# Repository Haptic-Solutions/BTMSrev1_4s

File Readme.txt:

Open Source Universal Battery Controller
Test battery is 4S Lithium Ion Pack
16.8V 2.6Ah rated. 38.48Wh Nominal
Please note that this device is a prototype and all features are still being extensively tested, some features aren't fully implement, and others are awaiting further polishing. Please excuse our mess as we continue to develop this system, it's documentation, and source/design repository.
Watch your step! The workshop is messy. ;)

	Though, this pack is worn out a bit as these are recycled cells. No worries though, as this BMS, Charger, and Power Management System will measure, and account for performance variations between batteries and chemistry types. Features include, but are not limited to:

    • BUCK-BOOST charge input to accommodate a wide range of battery configurations and supports charge voltage inputs from 5v-25v
    • USB-PD and USB2.0 charge to support a wide range of USB chargers up to 100watt.
    • AUX CHARGE PORT for solar applications
    • 2S, 3S, OR 4S support via jumper on the cell inputs
    • POWER SWITCH MODES ranging from push-and-hold, to automatic power on when charger power disconnected
    • FULL ACCESS to a wide range of settings such as cell max voltage and current
    • REDUNDANT SAFETY SYSTEMS not just in firmware but in hardware via over-voltage detection, shutdown, and disabling once any cell reaches 4.3v
    • ERROR REPORTING and TELEMETRY in a simple to access single letter command set via built-in USB serial or AUX UART header accessed by a terminal emulator
    • LCD SUPPORT via UART output that is configurable
    • HEATER CONTROL for cold environments with board and battery temperature sensors

Specs:
    • 25V 5A max charge input
    • 18V 10A max battery output, 2s-4s configurations, max 4.3v/cell
    • Dual UART with one dedicated to USB FTDI
    • dsPIC30F4011 micro-controller ~14mips
    • C codebase
    • 0.015mA deep-sleep (diode leakage, we aim to improve this)

Stay tuned for developments. We've got a lot of ground to cover before we release this into the wild! Our goal is to help other hobbyists be safer with batteries while getting their max performance in a very wide range of supported applications and cell chemistry types!
Copyright (2024) Haptic Solutions Inc.

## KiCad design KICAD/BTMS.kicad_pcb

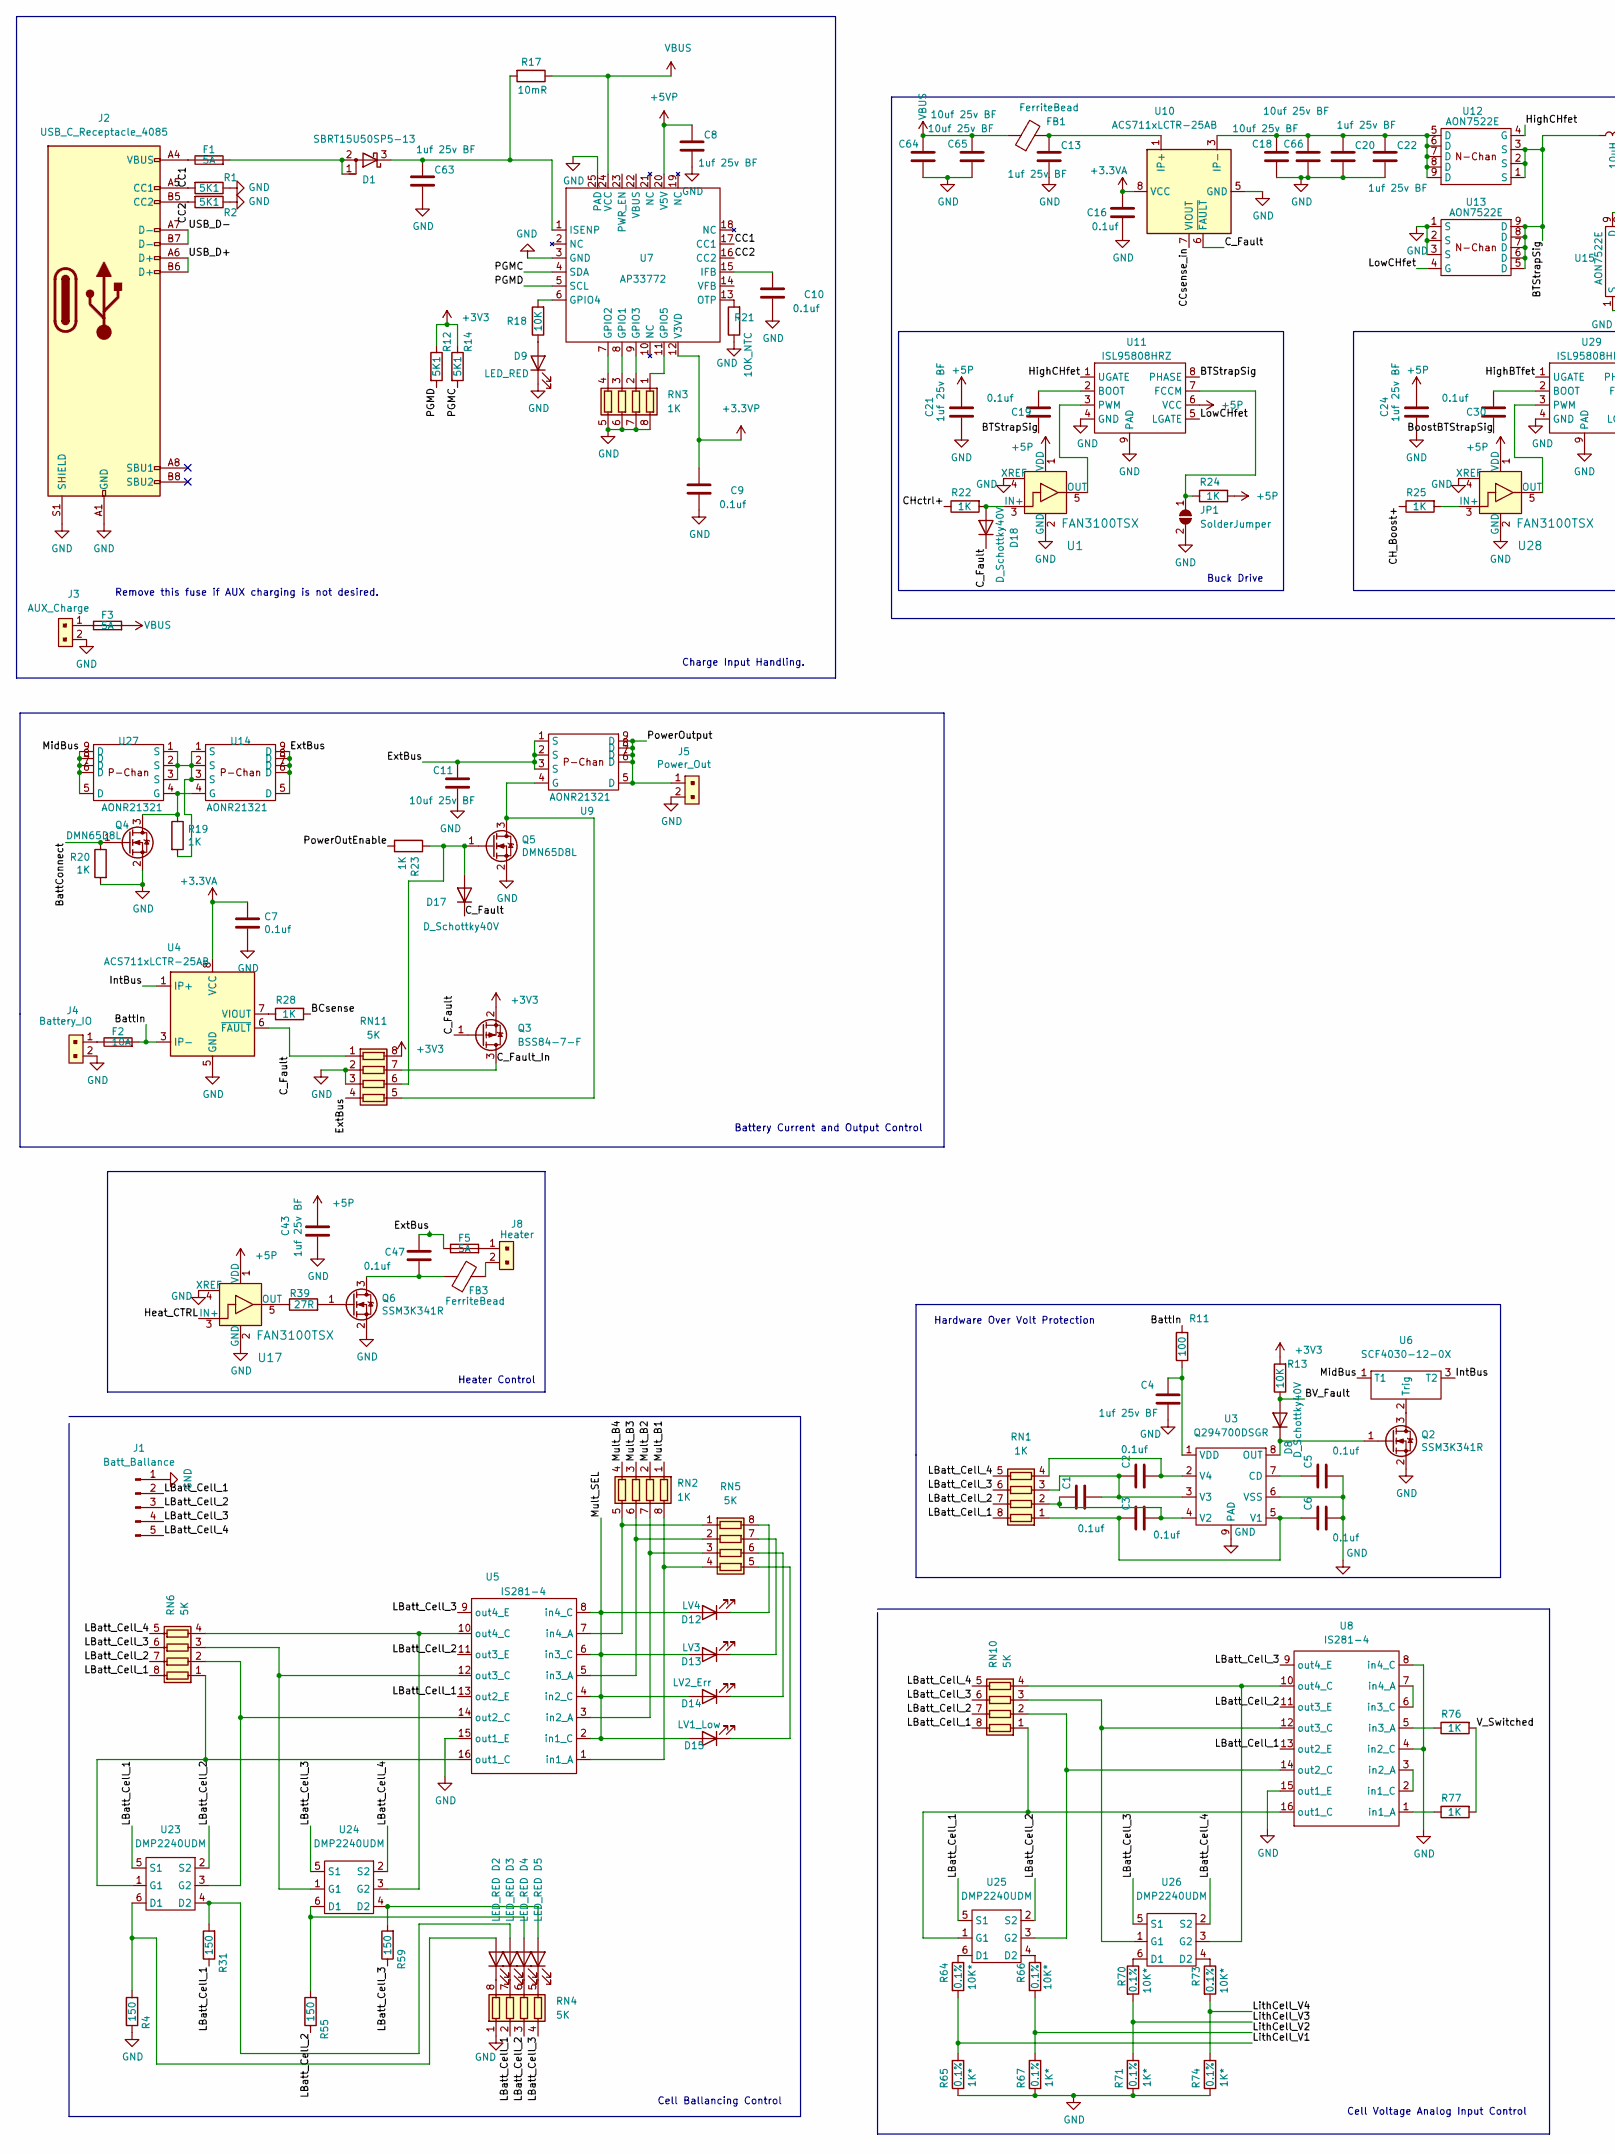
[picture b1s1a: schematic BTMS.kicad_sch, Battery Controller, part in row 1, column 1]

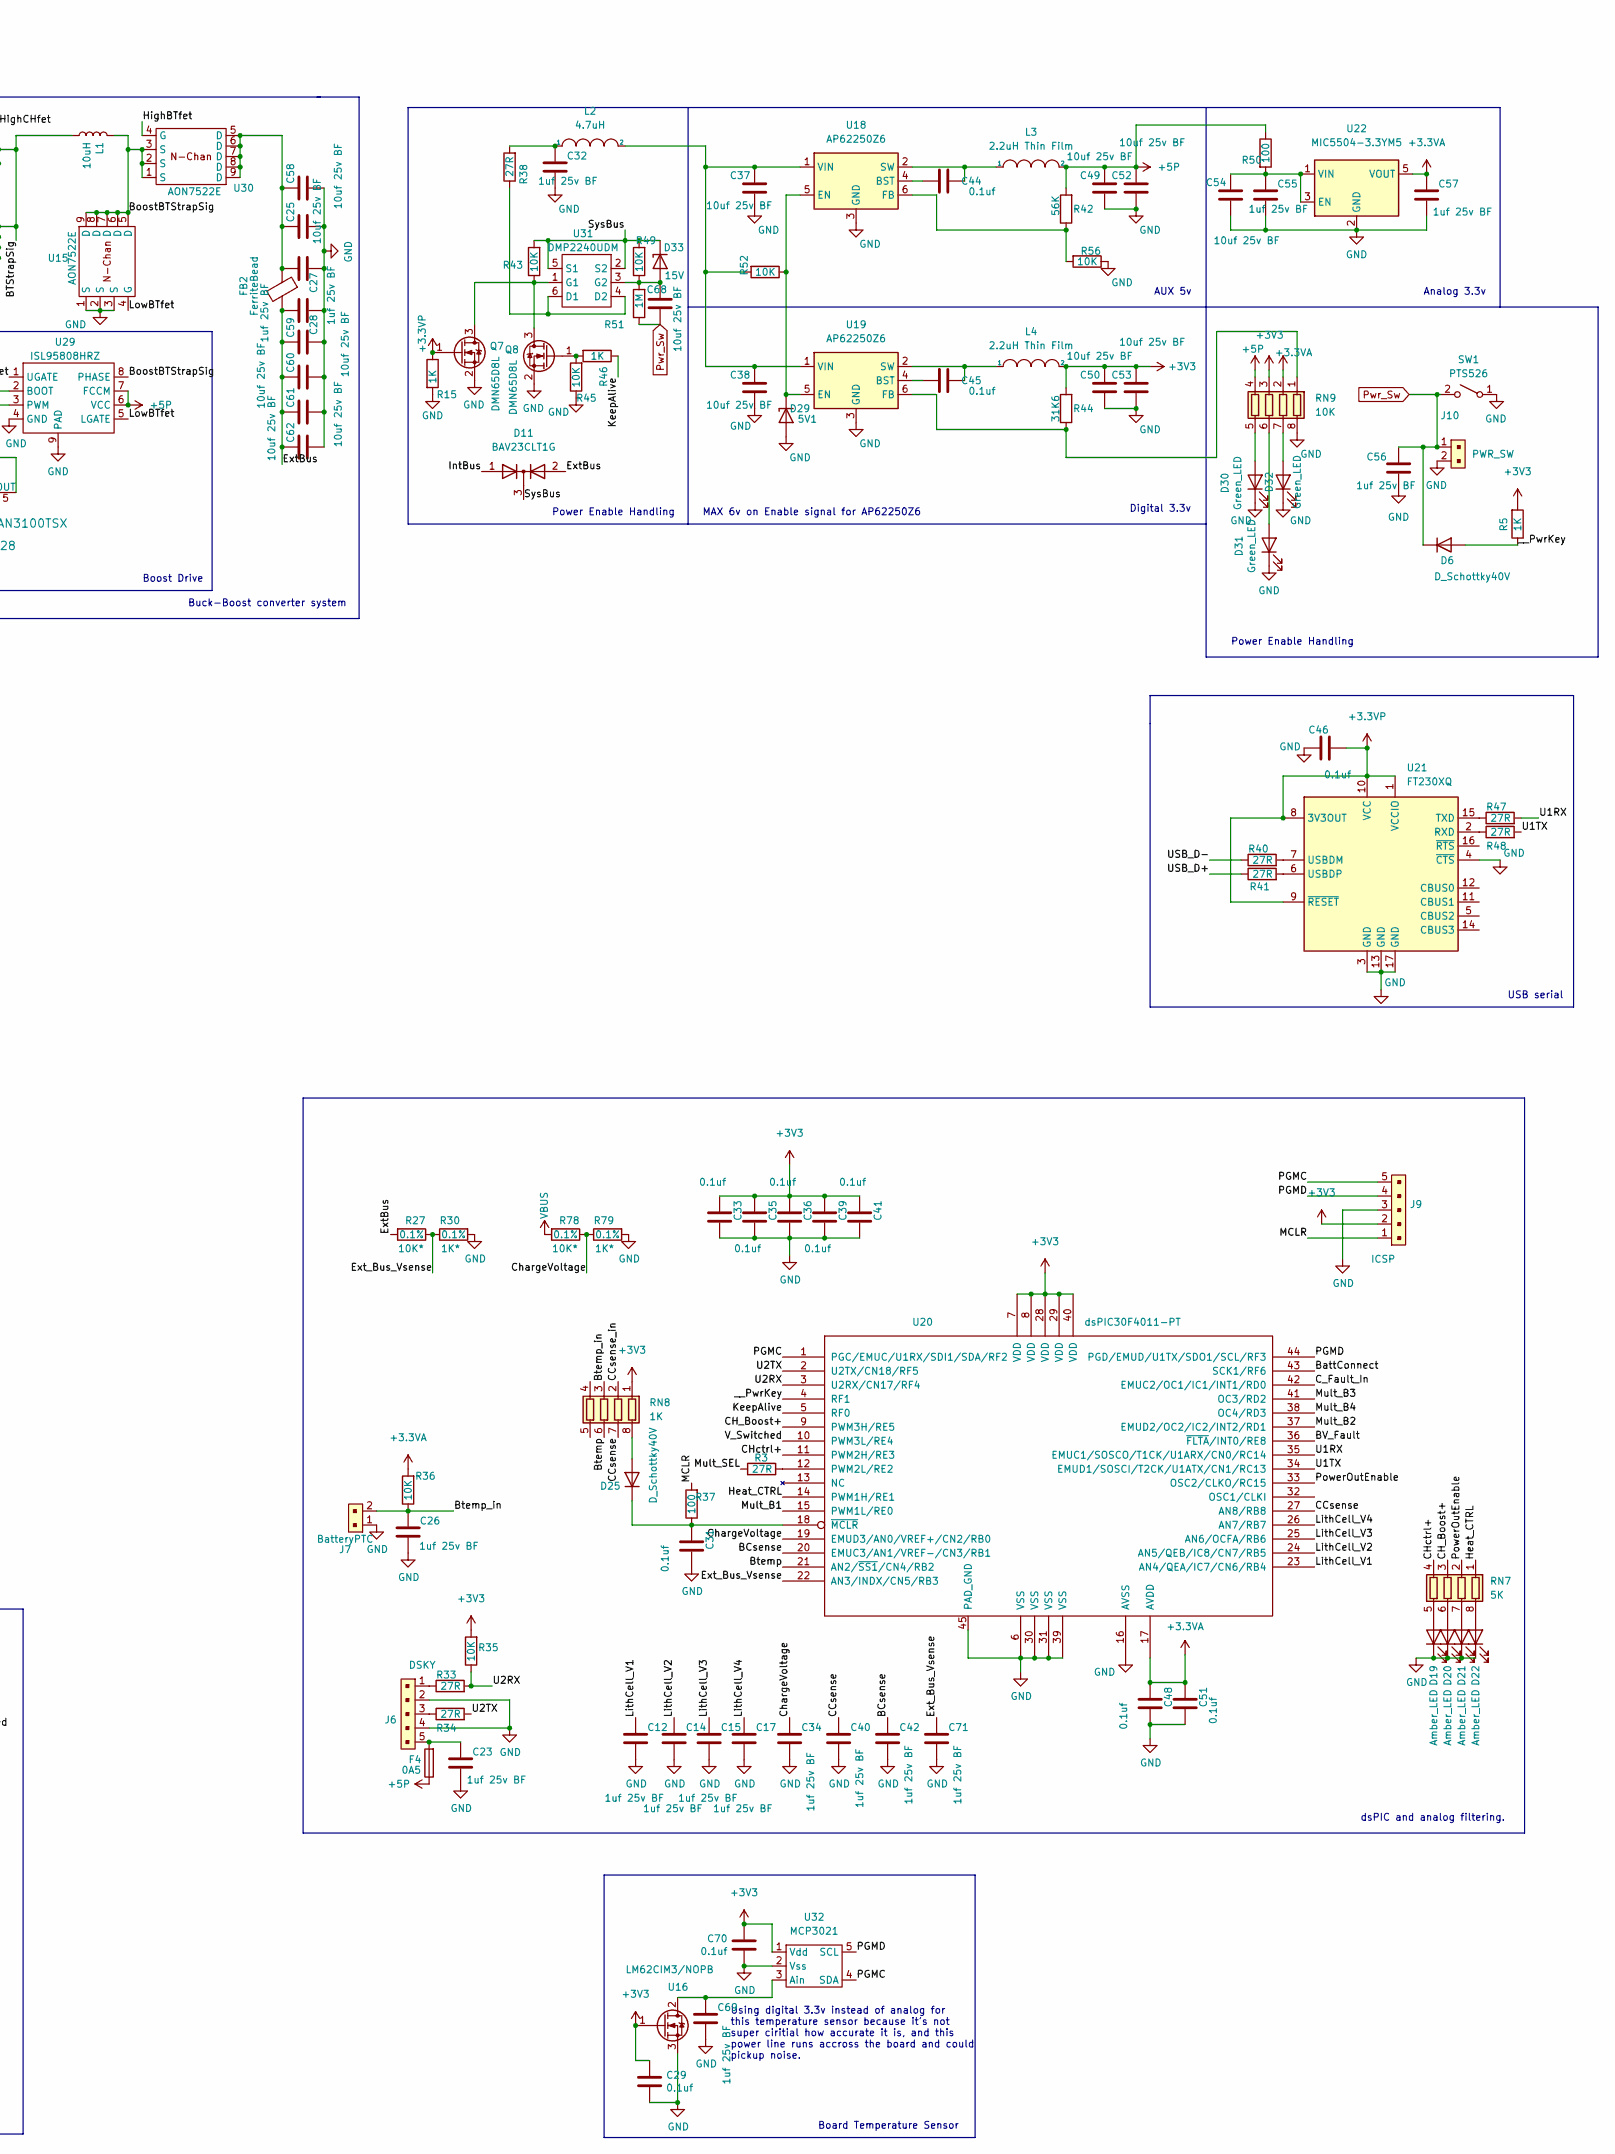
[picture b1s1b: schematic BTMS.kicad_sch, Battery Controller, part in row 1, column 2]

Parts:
C1, C2, C3, C5, C6, C7, C9, C10, C16, C19, C29, C30, C31, C33, C35, C36, C39, C41, C44, C45, C46, C47, C48, C51, C70: 0.1uf; C_0402_1005Metric; Digi-Key_PN 1276-1043-1-ND
C4, C8, C12, C13, C14, C15, C17, C20, C21, C22, C23, C24, C26, C27, C28, C32, C34, C40, C42, C43, C55, C56, C57, C63, C69, C71: 1uf 25v BF; C_0402_1005Metric; Digi-Key_PN 445-175215-1-ND
C11, C18, C25, C37, C38, C49, C50, C52, C53, C54, C58, C59, C60, C61, C62, C64, C65, C66, C68: 10uf 25v BF; C_0805_2012Metric; Digi-Key_PN 490-GRJ21BR61E106KE01KCT-ND
D1: SBRT15U50SP5-13; TO-277B; Digi-Key_PN SBRT15U50SP5-13DICT-ND
D2, D3, D4, D5, D9: LED_RED; LED_0603_1608Metric; Digi-Key_PN 732-4978-1-ND
D6, D8, D17, D18, D25: D_Schottky40V; D_0603_1608Metric; Digi-Key_PN CCS15S40L3FCT-ND
D11: BAV23CLT1G; SOT-23; Digi-Key_PN BAV23CLT1GOSCT-ND
D12: LV4; LED_0603_1608Metric; Digi-Key_PN 732-4978-1-ND
D13: LV3; LED_0603_1608Metric; Digi-Key_PN 732-4978-1-ND
D14: LV2_Err; LED_0603_1608Metric; Digi-Key_PN 732-4978-1-ND
D15: LV1_Low; LED_0603_1608Metric; Digi-Key_PN 732-4978-1-ND
D19, D20, D21, D22: Amber_LED; LED_0603_1608Metric; Digi-Key_PN 732-150060AS75000CT-ND
D29: 5V1; D_SOD-123; Digi-Key_PN MMSZ5231B-FDICT-ND
D30, D31, D32: Green_LED; LED_0603_1608Metric; Digi-Key_PN 732-4971-1-ND
D33: 15V; D_SOD-123; Digi-Key_PN DDZ15-7DICT-ND
F1, F3, F5: 5A; Fuse_1206_3216Metric; Digi-Key_PN 507-1886-1-ND
F2: 10A; Fuse_1206_3216Metric; Digi-Key_PN 507-1942-1-ND
F4: 0A5; Fuse_0603_1608Metric_Pad1.05x0.95mm_HandSolder; Digi-Key_PN 507-1089-1-ND
FB1, FB2, FB3: FerriteBead; R_1206_3216Metric; Digi-Key_PN 490-13269-1-ND
J1: Batt_Ballance; JST_EH_S5B-EH_1x05_P2.50mm_Horizontal; Digi-Key_PN 455-4228-ND
J2: USB_C_Receptacle_4085; USB_C_Receptacle_GCT_USB4085; Digi-Key_PN 2073-USB4085-GF-ACT-ND
J3: AUX_Charge; JST_VH_B2PS-VH_1x02_P3.96mm_Horizontal; MPN 22-23-2021
J4: Battery_IO; JST_VH_B2PS-VH_1x02_P3.96mm_Horizontal; MPN 22-23-2021
J5: Power_Out; JST_VH_B2PS-VH_1x02_P3.96mm_Horizontal; MPN 22-23-2021
J6: DSKY; PinHeader_1x05_P2.54mm_Vertical; MPN B5B-XH-A(LF)(SN)
J7: BatteryPTC; PinHeader_1x02_P2.54mm_Vertical; MPN 22-23-2021
J8: Heater; PinHeader_1x02_P2.54mm_Vertical; MPN 22-23-2021
J9: ICSP; PinHeader_1x05_P2.54mm_Vertical; MPN B5B-XH-A(LF)(SN)
J10: PWR_SW; PinHeader_1x02_P2.54mm_Vertical; MPN 22-23-2021
JP1: SolderJumper; SolderJumper-2_P1.3mm_Open_TrianglePad1.0x1.5mm
L1: 10uH; L_12x12mm_H4.5mm; Digi-Key_PN SRP1265A-100MCT-ND
L2: 4.7uH; IND_ASPI-4030S-4R7M-T; Digi-Key_PN 535-12322-1-ND
L3, L4: 2.2uH Thin Film; L_0805_2012Metric_Pad1.15x1.40mm_HandSolder; Digi-Key_PN 1276-6901-1-ND
Q2, Q6: SSM3K341R; SOT-23; Digi-Key_PN SSM3K341RLFCT-ND
Q3: BSS84-7-F; SOT-23; Digi-Key_PN BSS84-FDICT-ND
Q4, Q5, Q7, Q8: DMN65D8L; SOT-23; Digi-Key_PN DMN65D8L-7DICT-ND
R1, R2, R12, R14: 5K1; R_0603_1608Metric; Digi-Key_PN 13-RC0603FR-135K1LCT-ND
R3, R33, R34, R38, R39, R40, R41, R47, R48: 27R; R_0603_1608Metric; Digi-Key_PN 13-RC0603FR-1327RLCT-ND
R4, R31, R55, R59: 150; R_0805_2012Metric_Pad1.20x1.40mm_HandSolder; Digi-Key_PN 2019-RK73B2ATTD151JCT-ND
R5, R15, R19, R20, R22, R23, R24, R25, R28, R46, R76, R77: 1K; R_0603_1608Metric; Digi-Key_PN 311-1.00KHRCT-ND
R11, R37, R50: 100; R_0603_1608Metric; Digi-Key_PN 311-100HRCT-ND
R13, R18, R35, R36, R43, R45, R49, R52, R56: 10K; R_0603_1608Metric; Digi-Key_PN CR0603-FX-1002ELFCT-ND
R17: 10mR; R_1206_3216Metric; Digi-Key_PN CSR1206FT10L0CT-ND
R21: 10K_NTC; R_0603_1608Metric; Digi-Key_PN RMCF0603FT91K0CT-ND
R27, R64, R66, R70, R73, R78: 10K*; R_0603_1608Metric; Digi-Key_PN YAG1236CT-ND
R30, R65, R67, R71, R74, R79: 1K*; R_0603_1608Metric; Digi-Key_PN YAG1237CT-ND
R42: 56K; R_0603_1608Metric; Digi-Key_PN 311-56KHRCT-ND
R44: 31K6; R_0603_1608Metric; Digi-Key_PN RMCF0603FT31K6CT-ND
R51: 1M; R_0603_1608Metric
RN1, RN2, RN3, RN8: 1K; R_Array_Convex_4x0612; Digi-Key_PN CAY16-1001F4LFCT-ND
RN4, RN5, RN6, RN7, RN10, RN11: 5K; R_Array_Convex_4x0612; Digi-Key_PN CAY16-4991F4LFCT-ND
RN9: 10K; R_Array_Convex_4x0612; Digi-Key_PN CAY16-1002F4LFCT-ND
SW1: PTS526; SW_SPST_SKQG_WithStem; Digi-Key_PN CKN12221-1-ND
U1, U17, U28: FAN3100TSX; SOT-23-5; MPN FAN3100TSX; Digi-Key_PN FAN3100TSXCT-ND
U3: Q294700DSGR; WDFN-8-1EP_2x2mm_P0.5mm_EP0.8x1.2mm; Digi-Key_PN 296-34984-1-ND
U4, U10: ACS711xLCTR-25AB; SOIC-8_3.9x4.9mm_P1.27mm; Digi-Key_PN 620-1371-1-ND
U5, U8: IS281-4; SOIC-16_4.55x10.3mm_P1.27mm; Digi-Key_PN IS281-4CT-ND
U6: SCF4030-12-0X; Digi-Key_PN 283-SCF4030-12-04CT-ND
U7: AP33772; WQFN-24-1EP_4x4mm_P0.5mm_EP2.6x2.6mm; Digi-Key_PN 31-AP33772DKZ-13CT-ND
U9, U14, U27: AONR21321; DFN-8-1EP_3x3mm_P0.65mm_EP1.7x2.05mm; Digi-Key_PN 785-1797-1-ND
U11, U29: ISL95808HRZ; DFN-8-1EP_2x2mm_P0.5mm_EP0.8x1.6mm; Digi-Key_PN 20-ISL95808HRZ-TCT-ND
U12, U13, U15, U30: AON7522E; DFN-8-1EP_3x3mm_P0.65mm_EP1.7x2.05mm; Digi-Key_PN 785-1505-1-ND
U16: LM62CIM3/NOPB; SOT-23; Digi-Key_PN LM62CIM3/NOPBCT-ND
U18, U19: AP62250Z6; SOT-563; Digi-Key_PN 31-AP62250Z6-7CT-ND
U20: dsPIC30F4011-PT; QFN-44-1EP_8x8mm_P0.65mm_EP6.45x6.45mm; Digi-Key_PN DSPIC30F401130IML-ND
U21: FT230XQ; QFN-16-1EP_4x4mm_P0.65mm_EP2.1x2.1mm; Digi-Key_PN 768-1130-1-ND
U22: MIC5504-3.3YM5; SOT-23-5; Digi-Key_PN 576-4764-1-ND
U23, U24, U25, U26, U31: DMP2240UDM; SOT-23-6; Digi-Key_PN DMP2240UDMDICT-ND
U32: MCP3021; SOT-23-5; Digi-Key_PN MCP3021A5T-E/OTCT-ND

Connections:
+3.3VA: C7.1, C16.1, C48.1, C51.1, C57.1, R36.2, RN9.2 (R2.1), U4.8 (VCC), U10.8 (VCC), U20.17 (AVDD), U22.5 (VOUT)
+3.3VP: C9.1, C46.2, Q7.1 (G), R15.1, U7.12 (V3VD), U21.1 (VCCIO), U21.8 (3V3OUT), U21.9 (~RESET), U21.10 (VCC)
+3V3: C29.1, C33.1, C35.1, C36.1, C39.1, C41.1, C50.1, C53.1, C70.1, J9.2, L4.2, Q3.2 (S), R5.2, R12.1, R13.2, R14.1, R35.2, R44.2, RN8.1 (R1.1), RN9.3 (R3.1), RN11.8 (R1.2), U16.1 (G), U20.7 (VDD), U20.8 (VDD), U20.28 (VDD), U20.29 (VDD), U20.40 (VDD), U32.1 (Vdd)
+5P: C21.1, C24.1, C43.1, C49.1, C52.1, F4.1, L3.2, R24.2, R42.2, R50.1, RN9.4 (R4.1), U1.1 (VDD), U11.6 (VCC), U17.1 (VDD), U28.1 (VDD), U29.6 (VCC), U29.7 (FCCM)
+5VP: C8.1, U7.20 (V5V)
/BCsense: C42.1, R28.2, U20.20 (EMUC3/AN1/VREF-/CN3/RB1)
/BTStrapSig: C19.2, L1.1, U11.8 (PHASE), U12.1 (S), U12.2 (S), U12.3 (S), U13.5 (D), U13.6 (D), U13.7 (D), U13.8 (D), U13.9 (D)
/BV_Fault: D8.2 (A), R13.1, U20.36 (~FLTA/INT0/RE8)
/BattConnect: Q4.1 (G), R20.1, U20.43 (SCK1/RF6)
/BattIn: F2.2, R11.2, U4.3 (IP-), U4.4 (IP-)
/BoostBTStrapSig: C30.2, L1.2, U15.5 (D), U15.6 (D), U15.7 (D), U15.8 (D), U15.9 (D), U29.8 (PHASE), U30.1 (S), U30.2 (S), U30.3 (S)
/Btemp: RN8.6 (R3.2), U20.21 (AN2/~SS1/CN4/RB2)
/Btemp_in: C26.1, J7.2, R36.1, RN8.3 (R3.1)
/CC1: J2.A5 (CC1), R1.2, U7.17 (CC1)
/CC2: J2.B5 (CC2), R2.2, U7.16 (CC2)
/CCsense: C40.1, RN8.7 (R2.2), U20.27 (AN8/RB8)
/CCsense_in: RN8.2 (R2.1), U10.7 (VIOUT)
/CH_Boost+: R25.1, RN7.3 (R3.1), U20.9 (PWM3H/RE5)
/CHctrl+: R22.1, RN7.4 (R4.1), U20.11 (PWM2H/RE3)
/C_Fault: D17.1 (K), D18.1 (K), Q3.1 (G), RN11.1 (R1.1), U4.6 (~FAULT), U10.6 (~FAULT)
/C_Fault_In: Q3.3 (D), RN11.7 (R2.2), U20.42 (EMUC2/OC1/IC1/INT1/RD0)
/ChargeVoltage: C34.1, R78.1, R79.1, U20.19 (EMUD3/AN0/VREF+/CN2/RB0)
/ExtBus: C11.1, C28.1, C47.1, C59.1, C60.1, C61.1, C62.1, D11.2 (A), F5.1, FB2.2, R27.2, RN11.4 (R4.1), U9.1 (S), U9.2 (S), U9.3 (S), U14.5 (D), U14.6 (D), U14.7 (D), U14.8 (D), U14.9 (D)
/Ext_Bus_Vsense: C71.1, R27.1, R30.1, U20.22 (AN3/INDX/CN5/RB3)
/Heat_CTRL: RN7.1 (R1.1), U17.3 (IN+), U20.14 (PWM1H/RE1)
/HighBTfet: U29.1 (UGATE), U30.4 (G)
/HighCHfet: U11.1 (UGATE), U12.4 (G)
/IntBus: D11.1 (A), U4.1 (IP+), U4.2 (IP+), U6.3 (T2)
/KeepAlive: R46.1, U20.5 (RF0)
/LBatt_Cell_1: J1.2, R31.1, RN1.8 (R1.2), RN4.2 (R2.1), RN6.8 (R1.2), RN10.8 (R1.2), U5.13 (out2_E), U8.13 (out2_E), U23.5 (S1), U25.5 (S1)
/LBatt_Cell_2: J1.3, R55.1, RN1.7 (R2.2), RN4.3 (R3.1), RN6.7 (R2.2), RN10.7 (R2.2), U5.11 (out3_E), U8.11 (out3_E), U23.2 (S2), U25.2 (S2)
/LBatt_Cell_3: J1.4, R59.1, RN1.6 (R3.2), RN4.4 (R4.1), RN6.6 (R3.2), RN10.6 (R3.2), U5.9 (out4_E), U8.9 (out4_E), U24.5 (S1), U26.5 (S1)
/LBatt_Cell_4: J1.5, RN1.5 (R4.2), RN6.5 (R4.2), RN10.5 (R4.2), U24.2 (S2), U26.2 (S2)
/LithCell_V1: C12.1, R64.2, R65.2, U20.23 (AN4/QEA/IC7/CN6/RB4)
/LithCell_V2: C14.1, R66.2, R67.2, U20.24 (AN5/QEB/IC8/CN7/RB5)
/LithCell_V3: C15.1, R70.2, R71.2, U20.25 (AN6/OCFA/RB6)
/LithCell_V4: C17.1, R73.2, R74.2, U20.26 (AN7/RB7)
/LowBTfet: U15.4 (G), U29.5 (LGATE)
/LowCHfet: U11.5 (LGATE), U13.4 (G)
/MCLR: J9.1, R37.2
/MidBus: U6.1 (T1), U27.5 (D), U27.6 (D), U27.7 (D), U27.8 (D), U27.9 (D)
/Mult_B1: RN2.1 (R1.1), U20.15 (PWM1L/RE0)
/Mult_B2: RN2.2 (R2.1), U20.37 (EMUD2/OC2/IC2/INT2/RD1)
/Mult_B3: RN2.3 (R3.1), U20.41 (OC3/RD2)
/Mult_B4: RN2.4 (R4.1), U20.38 (OC4/RD3)
/Mult_SEL: D12.2 (A), D13.2 (A), D14.2 (A), D15.2 (A), R3.1, U5.2 (in1_C), U5.4 (in2_C), U5.6 (in3_C), U5.8 (in4_C)
/PGMC: J9.5, R14.2, U7.4 (SDA), U20.1 (PGC/EMUC/U1RX/SDI1/SDA/RF2), U32.4 (SDA)
/PGMD: J9.4, R12.2, U7.5 (SCL), U20.44 (PGD/EMUD/U1TX/SDO1/SCL/RF3), U32.5 (SCL)
/PowerOutEnable: R23.2, RN7.2 (R2.1), U20.33 (OSC2/CLKO/RC15)
/PowerOutput: J5.1, U9.5 (D), U9.6 (D), U9.7 (D), U9.8 (D), U9.9 (D)
/SysBus: D11.3 (K), D33.1 (K), R43.2, R49.2, U31.2 (S2), U31.5 (S1)
/U1RX: R47.2, U20.35 (EMUC1/SOSCO/T1CK/U1ARX/CN0/RC14)
/U1TX: R48.2, U20.34 (EMUD1/SOSCI/T2CK/U1ATX/CN1/RC13)
/U2RX: R33.2, R35.1, U20.3 (U2RX/CN17/RF4)
/U2TX: R34.2, U20.2 (U2TX/CN18/RF5)
/USB_D+: J2.A6 (D+), J2.B6 (D+), R41.1
/USB_D-: J2.A7 (D-), J2.B7 (D-), R40.1
/V_Switched: R76.2, R77.2, U20.10 (PWM3L/RE4)
/__PwrKey: D6.2 (A), R5.1, U20.4 (RF1)
GND: C4.2, C5.2, C6.2, C7.2, C8.2, C9.2, C10.2, C11.2, C12.2, C13.2, C14.2, C15.2, C16.2, C17.2, C18.2, C20.2, C21.2, C22.2, C23.2, C24.2, C25.2, C26.2, C27.2, C28.2, C29.2, C31.2, C32.2, C33.2, C34.2, C35.2, C36.2, C37.2, C38.2, C39.2, C40.2, C41.2, C42.2, C43.2, C46.1, C48.2, C49.2, C50.2, C51.2, C52.2, C53.2, C54.2, C55.2, C56.2, C57.2, C58.2, C59.2, C60.2, C61.2, C62.2, C63.2, C64.2, C65.2, C66.2, C69.2, C70.2, C71.2, D9.1 (K), D19.1 (K), D20.1 (K), D21.1 (K), D22.1 (K), D29.2 (A), D30.1 (K), D31.1 (K), D32.1 (K), J1.1, J2.A1 (GND), J2.A12 (GND), J2.B1 (GND), J2.B12 (GND), J2.S1 (SHIELD), J3.2, J4.2, J5.2, J6.2, J6.4, J7.1, J9.3, J10.2, JP1.2 (B), Q2.2 (S), Q4.2 (S), Q5.2 (S), Q6.2 (S), Q7.2 (S), Q8.2 (S), R1.1, R2.1, R4.1, R15.2, R20.2, R21.1, R30.2, R45.1, R56.1, R65.1, R67.1, R71.1, R74.1, R79.2, RN3.5 (R4.2), RN3.6 (R3.2), RN3.7 (R2.2), RN3.8 (R1.2), RN4.1 (R1.1), RN9.8 (R1.2), RN11.2 (R2.1), RN11.3 (R3.1), SW1.1 (A), U1.2 (GND), U1.4 (XREF), U3.6 (VSS), U3.9 (PAD), U4.5 (GND), U5.15 (out1_E), U7.3 (GND), U7.25 (PAD), U8.4 (in2_C), U8.8 (in4_C), U8.15 (out1_E), U10.5 (GND), U11.4 (GND), U11.9 (PAD), U13.1 (S), U13.2 (S), U13.3 (S), U15.1 (S), U15.2 (S), U15.3 (S), U16.3 (S), U17.2 (GND), U17.4 (XREF), U18.3 (GND), U19.3 (GND), U20.6 (VSS), U20.16 (AVSS), U20.30 (VSS), U20.31 (VSS), U20.39 (VSS), U20.45 (PAD_GND), U21.3 (GND), U21.4 (~CTS), U21.13 (GND), U21.17 (GND), U22.2 (GND), U28.2 (GND), U28.4 (XREF), U29.4 (GND), U29.9 (PAD), U32.2 (Vss)
unnamed: C1.1, C3.2, RN1.2 (R2.1), U3.4 (V2)
unnamed: C1.2, C2.1, RN1.3 (R3.1), U3.3 (V3)
unnamed: C2.2, RN1.4 (R4.1), U3.2 (V4)
unnamed: C3.1, C6.1, RN1.1 (R1.1), U3.5 (V1)
unnamed: C4.1, R11.1, U3.1 (VDD)
unnamed: C5.1, U3.7 (CD)
unnamed: C10.1, U7.15 (IFB)
unnamed: C13.1, FB1.2, U10.1 (IP+), U10.2 (IP+)
unnamed: C18.1, C20.1, C22.1, C66.1, U10.3 (IP-), U10.4 (IP-), U12.5 (D), U12.6 (D), U12.7 (D), U12.8 (D), U12.9 (D)
unnamed: C19.1, U11.2 (BOOT)
unnamed: C23.1, F4.2, J6.5
unnamed: C25.1, C27.1, C58.1, FB2.1, U30.5 (D), U30.6 (D), U30.7 (D), U30.8 (D), U30.9 (D)
unnamed: C30.1, U29.2 (BOOT)
unnamed: C31.1, D25.1 (K), R37.1, U20.18 (~MCLR)
unnamed: C32.1, L2.1, R38.2
unnamed: C37.1, C38.1, L2.2, R52.2, U18.1 (VIN), U19.1 (VIN)
unnamed: C44.1, U18.4 (BST)
unnamed: C44.2, L3.1, U18.2 (SW)
unnamed: C45.1, U19.4 (BST)
unnamed: C45.2, L4.1, U19.2 (SW)
unnamed: C47.2, FB3.1, Q6.3 (D)
unnamed: C54.1, C55.1, R50.2, U22.1 (VIN), U22.3 (EN)
unnamed: C63.1, D1.3 (K), R17.2, U7.1 (ISENP)
unnamed: C68.1, D33.2 (A), R49.1, R51.2, U31.3 (G2)
unnamed: C69.1, U16.2 (D), U32.3 (Ain)
unnamed: D1.1 (A), D1.2 (A), F1.2
unnamed: D2.1 (K), RN4.8 (R1.2)
unnamed: D2.2 (A), R4.2, U23.6 (D1)
unnamed: D3.1 (K), RN4.7 (R2.2)
unnamed: D3.2 (A), R31.2, U23.4 (D2)
unnamed: D4.1 (K), RN4.6 (R3.2)
unnamed: D4.2 (A), R55.2, U24.6 (D1)
unnamed: D5.1 (K), RN4.5 (R4.2)
unnamed: D5.2 (A), R59.2, U24.4 (D2)
unnamed: D8.1 (K), Q2.1 (G), U3.8 (OUT)
unnamed: D9.2 (A), R18.1
unnamed: D12.1 (K), RN5.8 (R1.2)
unnamed: D13.1 (K), RN5.7 (R2.2)
unnamed: D14.1 (K), RN5.6 (R3.2)
unnamed: D15.1 (K), RN5.5 (R4.2)
unnamed: D17.2 (A), Q5.1 (G), R23.1, RN11.6 (R3.2)
unnamed: D18.2 (A), R22.2, U1.3 (IN+)
unnamed: D19.2 (A), RN7.5 (R4.2)
unnamed: D20.2 (A), RN7.6 (R3.2)
unnamed: D21.2 (A), RN7.7 (R2.2)
unnamed: D22.2 (A), RN7.8 (R1.2)
unnamed: D25.2 (A), RN8.8 (R1.2)
unnamed: D29.1 (K), R52.1, U18.5 (EN), U19.5 (EN)
unnamed: D30.2 (A), RN9.5 (R4.2)
unnamed: D31.2 (A), RN9.6 (R3.2)
unnamed: D32.2 (A), RN9.7 (R2.2)
unnamed: F1.1, J2.A4 (VBUS), J2.A9 (VBUS), J2.B4 (VBUS), J2.B9 (VBUS)
unnamed: F2.1, J4.1
unnamed: F3.1, J3.1
unnamed: F5.2, J8.1
unnamed: FB3.2, J8.2
unnamed: J6.1, R33.1
unnamed: J6.3, R34.1
unnamed: JP1.1 (A), R24.1, U11.7 (FCCM)
unnamed: Q2.3 (D), U6.2 (Trig)
unnamed: Q4.3 (D), R19.1, U14.4 (G), U27.4 (G)
unnamed: Q5.3 (D), RN11.5 (R4.2), U9.4 (G)
unnamed: Q6.1 (G), R39.2
unnamed: Q7.3 (D), Q8.3 (D), R43.1, U31.1 (G1)
unnamed: Q8.1 (G), R45.2, R46.2
unnamed: R3.2, U20.12 (PWM2L/RE2)
unnamed: R18.2, U7.6 (GPIO4)
unnamed: R19.2, U14.1 (S), U14.2 (S), U14.3 (S), U27.1 (S), U27.2 (S), U27.3 (S)
unnamed: R21.2, U7.13 (OTP)
unnamed: R25.2, U28.3 (IN+)
unnamed: R28.1, U4.7 (VIOUT)
unnamed: R38.1, U31.4 (D2), U31.6 (D1)
unnamed: R39.1, U17.5 (OUT)
unnamed: R40.2, U21.7 (USBDM)
unnamed: R41.2, U21.6 (USBDP)
unnamed: R42.1, R56.2, U18.6 (FB)
unnamed: R44.1, RN9.1 (R1.1), U19.6 (FB)
unnamed: R47.1, U21.15 (TXD)
unnamed: R48.1, U21.2 (RXD)
unnamed: R64.1, U25.6 (D1)
unnamed: R66.1, U25.4 (D2)
unnamed: R70.1, U26.6 (D1)
unnamed: R73.1, U26.4 (D2)
unnamed: R76.1, U8.5 (in3_A)
unnamed: R77.1, U8.1 (in1_A)
unnamed: RN2.5 (R4.2), RN5.1 (R1.1), U5.7 (in4_A)
unnamed: RN2.6 (R3.2), RN5.2 (R2.1), U5.5 (in3_A)
unnamed: RN2.7 (R2.2), RN5.3 (R3.1), U5.3 (in2_A)
unnamed: RN2.8 (R1.2), RN5.4 (R4.1), U5.1 (in1_A)
unnamed: RN3.1 (R1.1), U7.11 (GPIO5)
unnamed: RN3.2 (R2.1), U7.9 (GPIO3)
unnamed: RN3.3 (R3.1), U7.8 (GPIO1)
unnamed: RN3.4 (R4.1), U7.7 (GPIO2)
unnamed: RN6.1 (R1.1), U5.16 (out1_C), U23.1 (G1)
unnamed: RN6.2 (R2.1), U5.14 (out2_C), U23.3 (G2)
unnamed: RN6.3 (R3.1), U5.12 (out3_C), U24.1 (G1)
unnamed: RN6.4 (R4.1), U5.10 (out4_C), U24.3 (G2)
unnamed: RN10.1 (R1.1), U8.16 (out1_C), U25.1 (G1)
unnamed: RN10.2 (R2.1), U8.14 (out2_C), U25.3 (G2)
unnamed: RN10.3 (R3.1), U8.12 (out3_C), U26.1 (G1)
unnamed: RN10.4 (R4.1), U8.10 (out4_C), U26.3 (G2)
unnamed: U1.5 (OUT), U11.3 (PWM)
unnamed: U8.2 (in1_C), U8.3 (in2_A)
unnamed: U8.6 (in3_C), U8.7 (in4_A)
unnamed: U28.5 (OUT), U29.3 (PWM)
Pwr_Sw: C56.1, C68.2, D6.1 (K), J10.1, R51.1, SW1.2 (B)
VBUS: C64.1, C65.1, F3.2, FB1.1, R17.1, R78.2, U7.24 (VCC)

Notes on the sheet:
USB serial
Power Enable Handling
Remove this fuse if AUX charging is not desired.
AUX 5v
Cell Voltage Analog Input Control
Buck-Boost converter system
Buck Drive
Board Temperature Sensor
Battery Current and Output Control
Heater Control
dsPIC and analog filtering.
Boost Drive
Cell Ballancing Control
MAX 6v on Enable signal for AP62250Z6
Hardware Over Volt Protection
Digital 3.3v
Analog 3.3v
Using digital 3.3v instead of analog for this temperature sensor because it's not super ciritial how accurate it is, and this power line runs accross the board and could pickup noise.
Charge Input Handling.

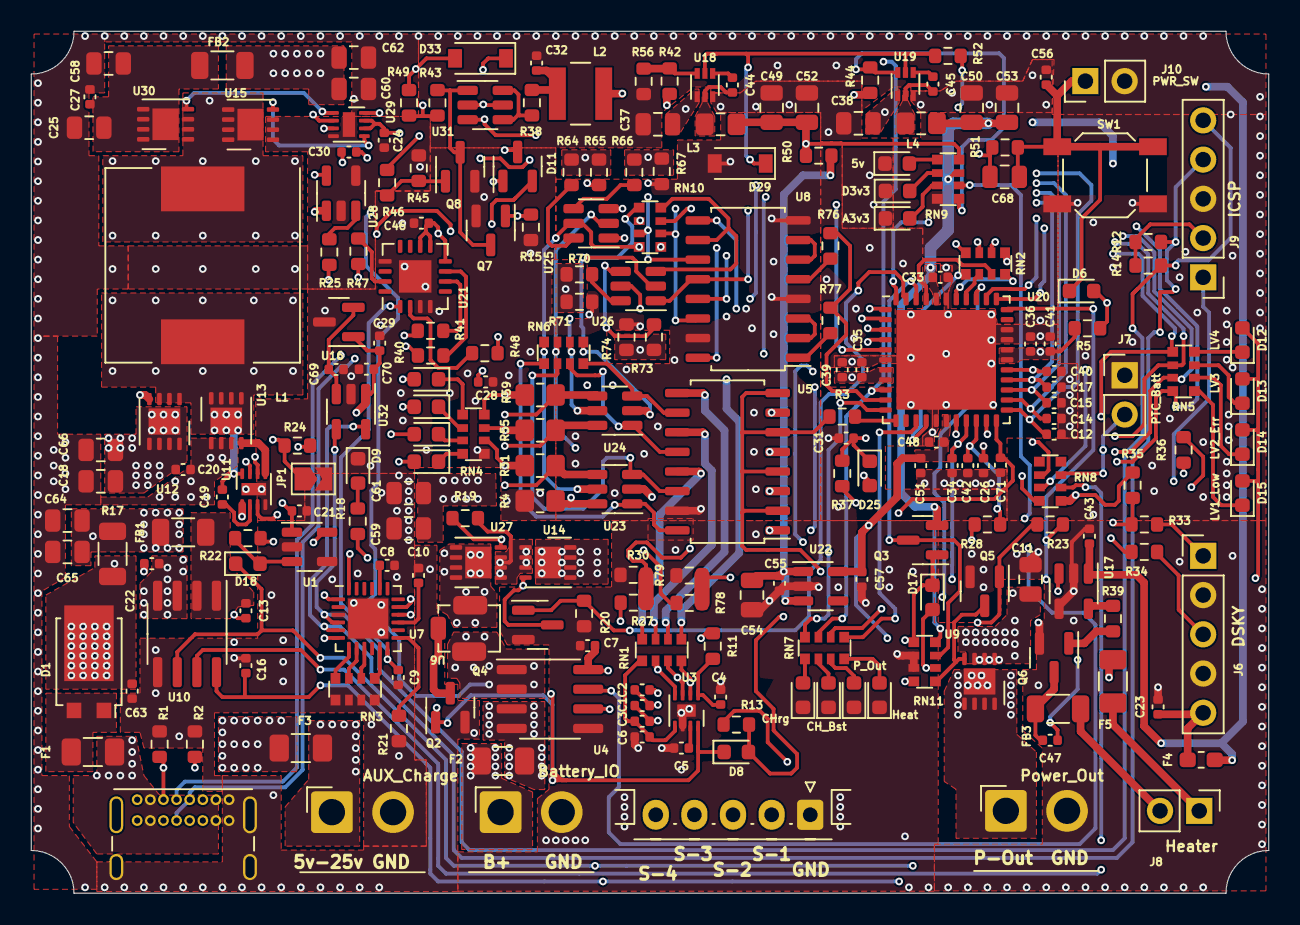
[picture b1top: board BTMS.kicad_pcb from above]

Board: 4 copper layers, 80.1 x 55.8 mm, 226 parts (0 on the bottom side), 167 nets.
